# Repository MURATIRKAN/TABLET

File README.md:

# TABLET
LOKUM-MINI TABLET ALLWINNER A33 ARM-CPU

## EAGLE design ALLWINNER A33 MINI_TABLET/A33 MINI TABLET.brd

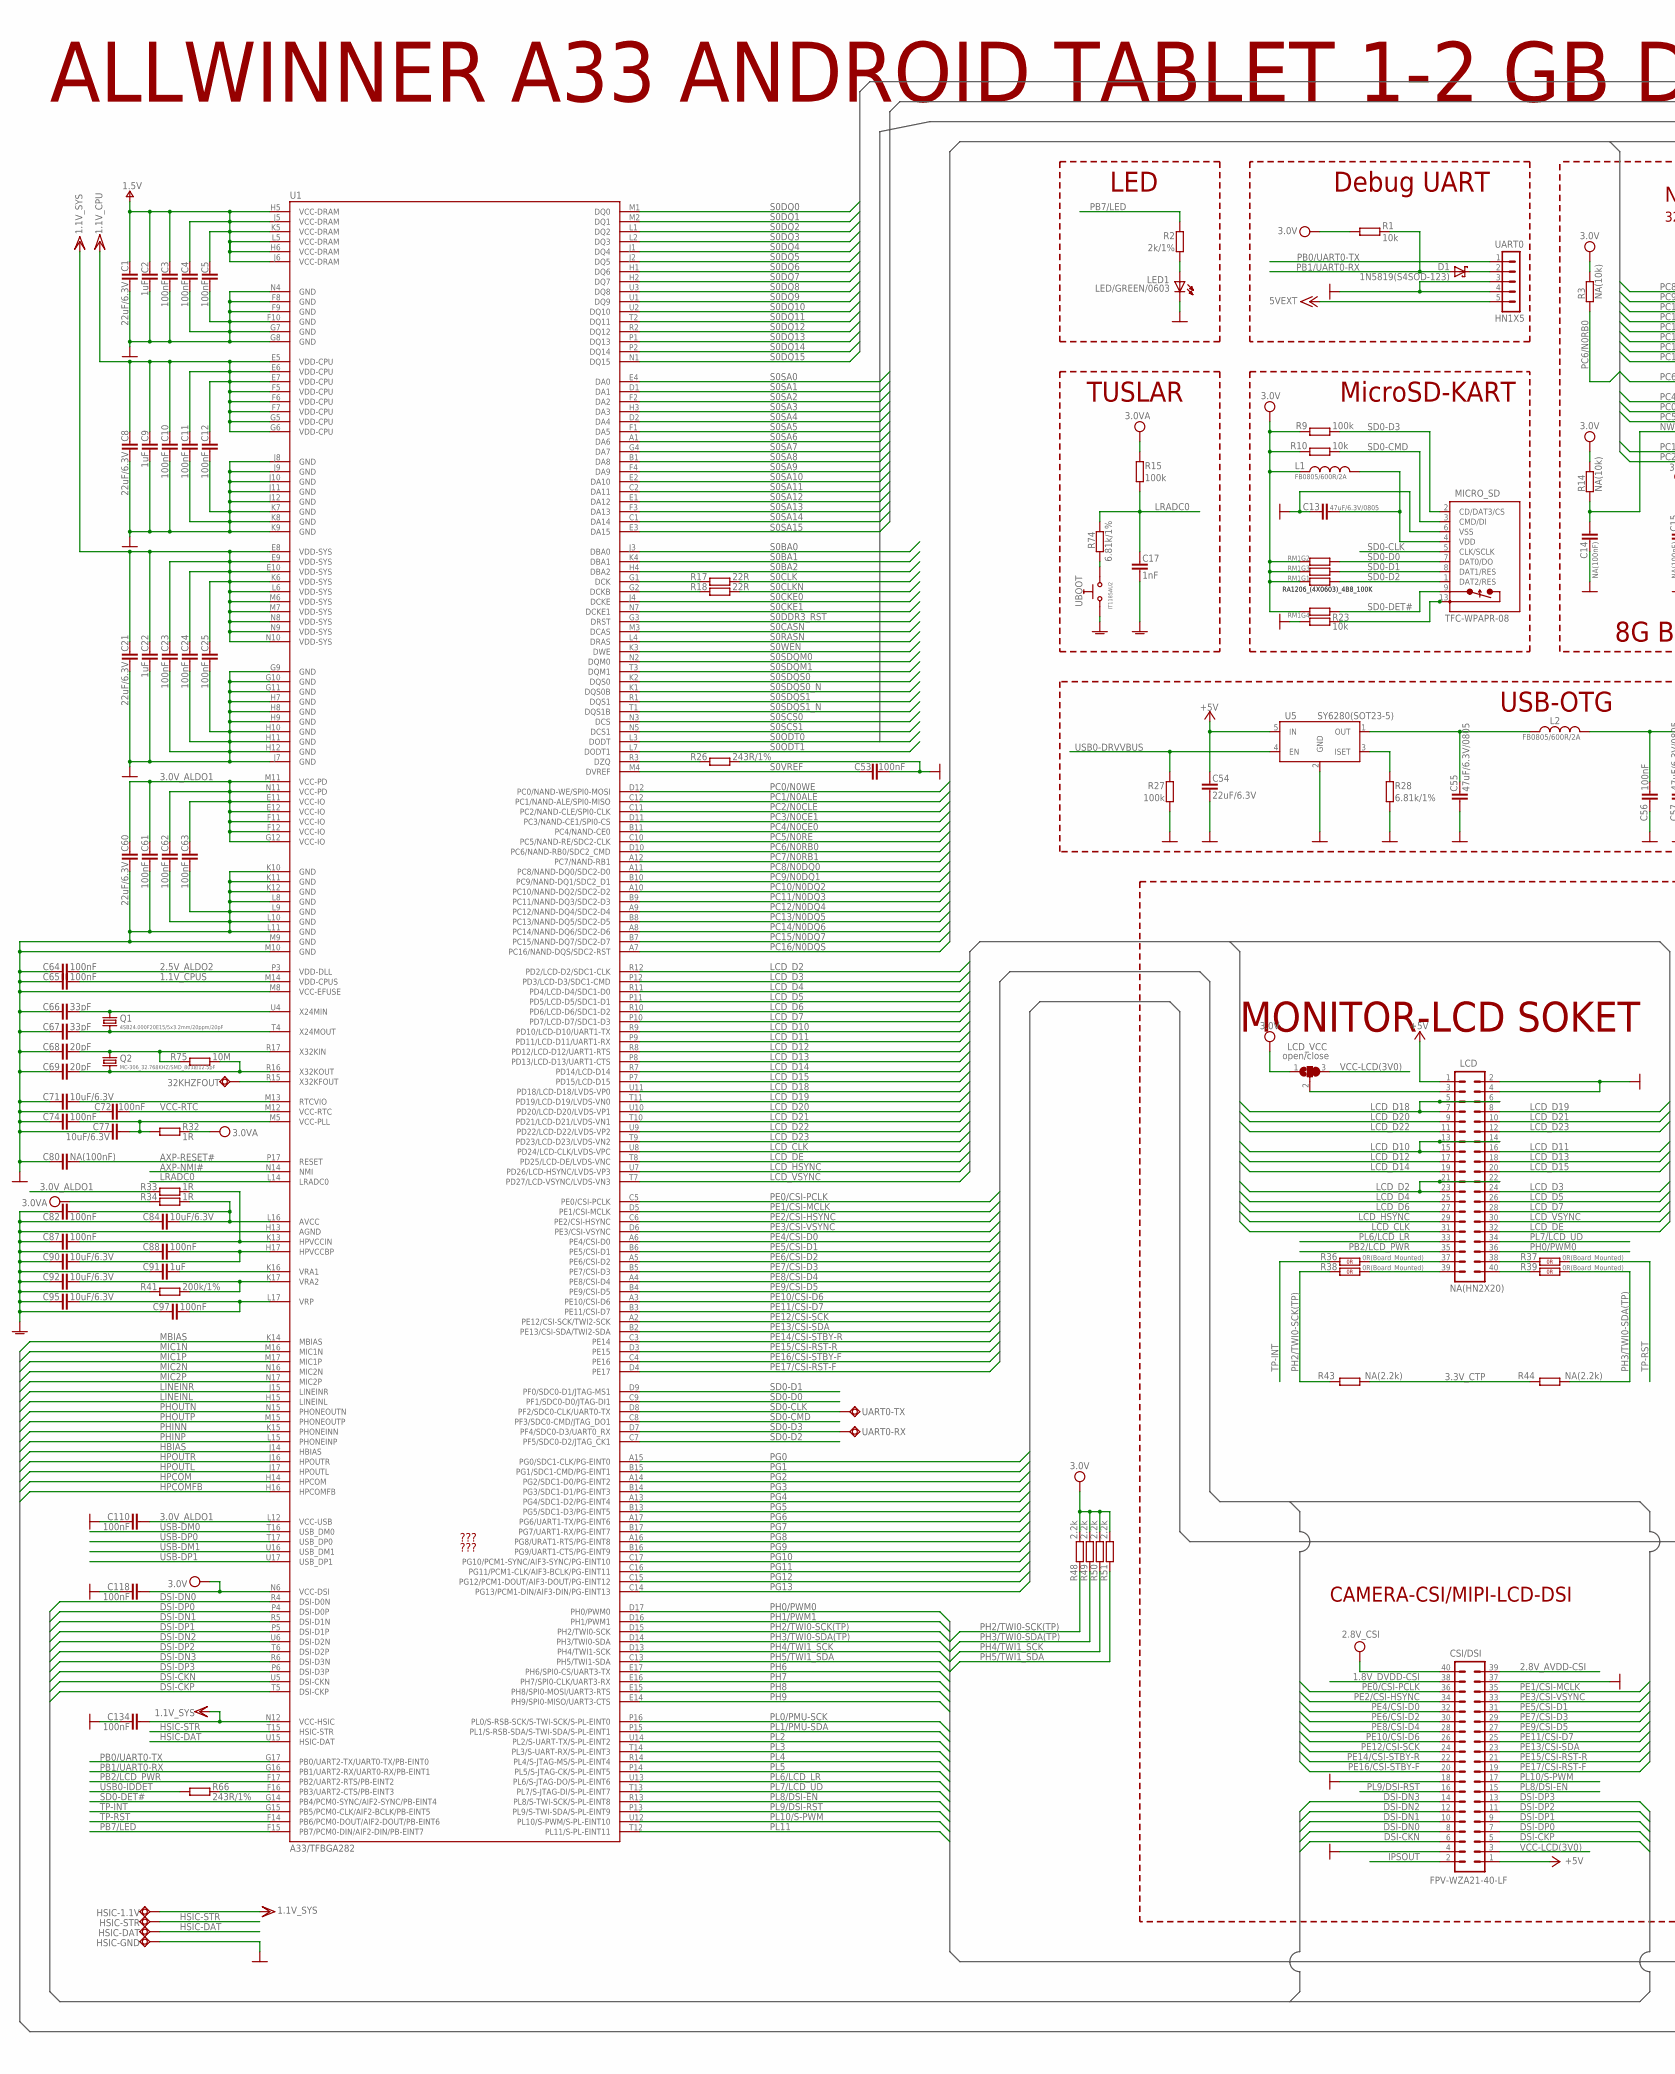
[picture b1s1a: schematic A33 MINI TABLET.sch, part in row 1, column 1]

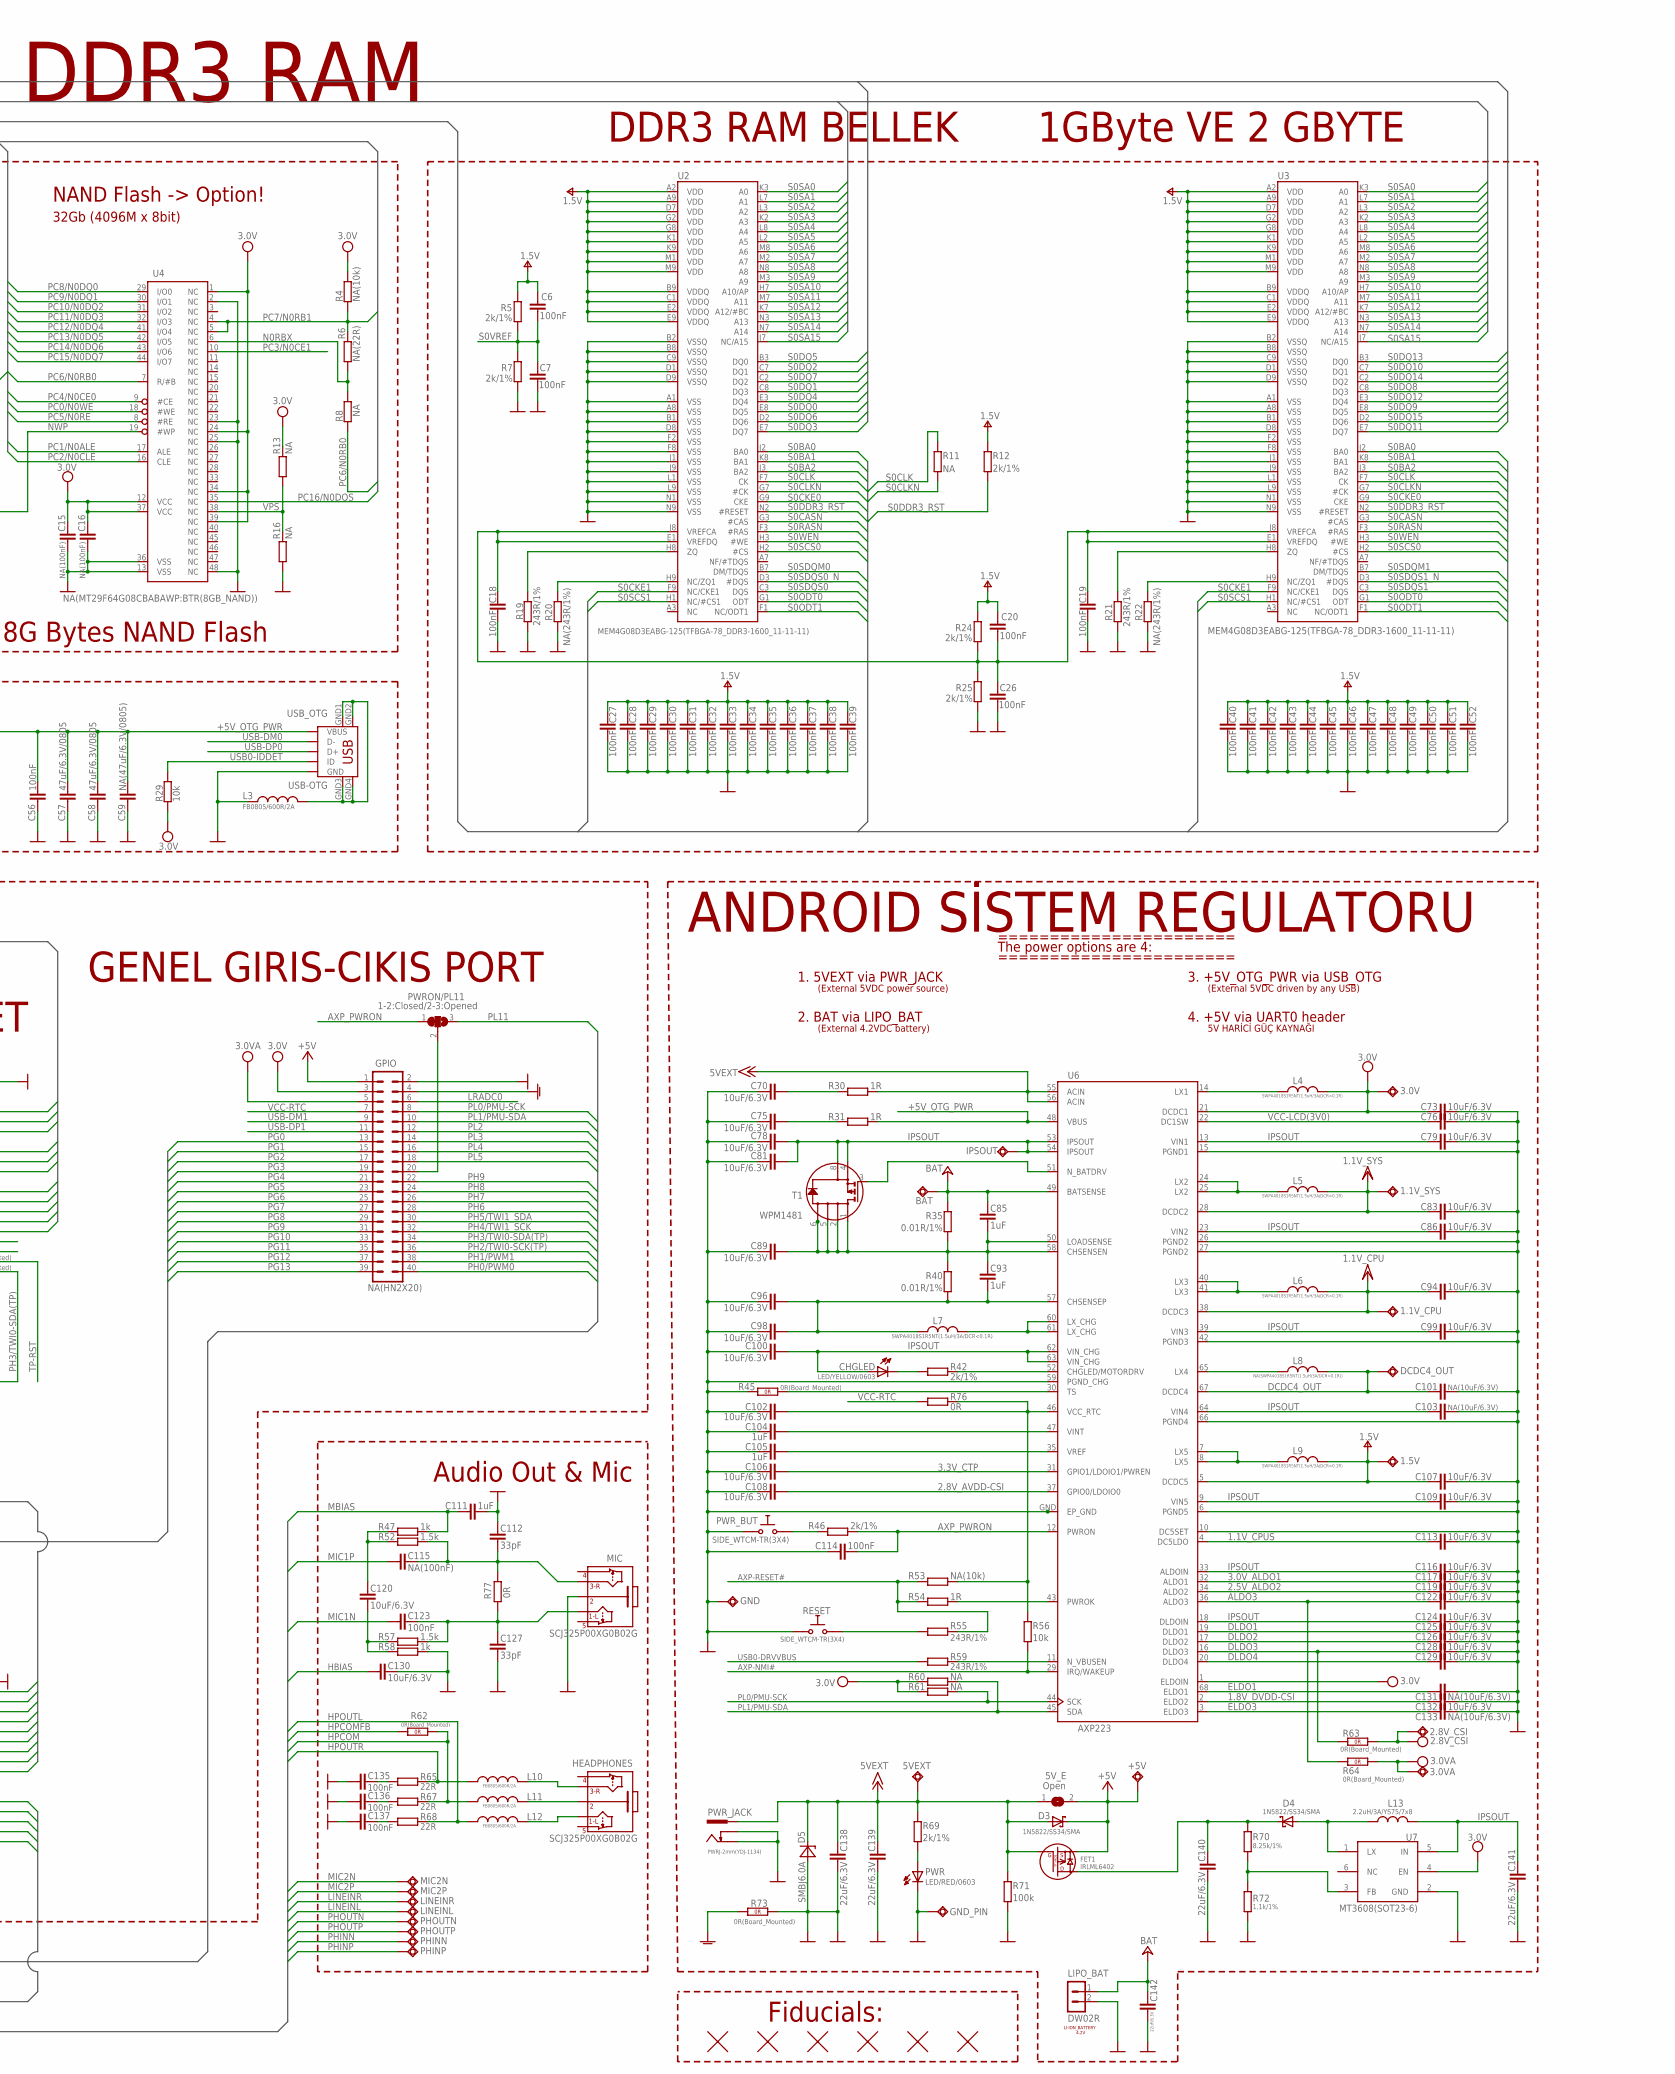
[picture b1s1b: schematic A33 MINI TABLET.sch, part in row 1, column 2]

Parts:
1.1V_CPU, 1.1V_SYS, 1.5V, 2.8V_CSI, 3.0V, 3.0VA, 5VEXT, 32KHZFOUT: TESTPADTESTPAD_40-ROUND; TESTPAD_40-ROUND
5V_E: Open; SJ_1_SMALLER
+5V: TESTPADTESTPAD_40-ROUND; TESTPAD_40-ROUND
BAT: TESTPADTESTPAD_40-ROUND; TESTPAD_40-ROUND
C1, C8, C21, C54, C60, C138, C139, C140, C141, C142: 22uF/6.3V; C0603_DWS
C2, C9, C22, C85, C91, C93, C104, C105, C111: 1uF; C0603_DWS
C3, C4, C5, C6, C7, C10, C11, C12, C18, C19, C20, C23, C24, C25, C26, C27, C28, C29, C30, C31, C32, C33, C34, C35, C36, C37, C38, C39, C40, C41, C42, C43, C44, C45, C46, C47, C48, C49, C50, C51, C52, C53, C56, C61, C62, C63, C64, C65, C72, C74, C82, C87, C88, C97, C110, C114, C118, C123, C134, C135, C136, C137: 100nF; C0402_TI
C13, C55, C57, C58: 47uF/6.3V/0805; C0805_5MIL_DWS
C14, C15, C16, C80, C115: NA(100nF); C0402_TI
C17: 1nF; C0603_DWS
C59: NA(47uF/6.3V/0805); C0805_5MIL_DWS
C66, C67, C112, C127: 33pF; C0603_DWS
C68, C69: 20pF; C0603_DWS
C70, C71, C73, C75, C76, C77, C78, C79, C81, C83, C84, C86, C89, C90, C92, C94, C95, C96, C98, C99, C100, C102, C106, C107, C108, C109, C113, C116, C117, C119, C120, C122, C124, C125, C126, C128, C129, C130, C132: 10uF/6.3V; C0603_DWS
C101, C103, C131, C133: NA(10uF/6.3V); C0603_DWS
CHGLED: LED/YELLOW/0603; LED-0603_TEST
CSI/DSI: FPV-WZA21-40-LF
D1: 1N5819(S4SOD-123); SOD-123
D3, D4: 1N5822/SS34/SMA; MLL-41
D5: SMBJ6.0A; DO214AA
DCDC4_OUT: TESTPADTESTPAD_40-ROUND; TESTPAD_40-ROUND
FET1: IRLML6402; SOT23
GND: TESTPADTESTPAD_40-ROUND; TESTPAD_40-ROUND
GND_PIN: TESTPAD3; TEST_PAD40/70/SQUARE
GPIO: NA(HN2X20); HN2X20-MALE
HEADPHONES: SCJ325P00XG0B02G
HSIC-1.1V: TESTPADTESTPAD_40-ROUND; TESTPAD_40-ROUND
HSIC-DAT: TESTPADTESTPAD_40-ROUND; TESTPAD_40-ROUND
HSIC-GND: TESTPADTESTPAD_40-ROUND; TESTPAD_40-ROUND
HSIC-STR: TESTPADTESTPAD_40-ROUND; TESTPAD_40-ROUND
IPSOUT: TESTPADTESTPAD_40-ROUND; TESTPAD_40-ROUND
L1, L2, L3, L10, L11, L12: FB0805/600R/2A; L0805_5MIL_DWS
L4, L5, L6, L7, L9: SWPA4018S1R5NT(1.5uH/3A/DCR<0.1R); SWPA4018S
L8: NA(SWPA4018S1R5NT(1.5uH/3A/DCR<0.1R)); SWPA4018S
L13: 2.2uH/3A/YS75/7x8; 8X8MM_3131
LCD: NA(HN2X20); HN2X20-MALE
LCD_VCC: open/close; SJ_2_SMALL_23_TIED
LED1: LED/GREEN/0603; LED-0603_TEST
LINEINL: TESTPADTESTPAD_40-ROUND; TESTPAD_40-ROUND
LINEINR: TESTPADTESTPAD_40-ROUND; TESTPAD_40-ROUND
LIPO_BAT: DW02R
MIC: SCJ325P00XG0B02G
MIC2N, MIC2P: TESTPADTESTPAD_40-ROUND; TESTPAD_40-ROUND
MICRO_SD: TFC-WPAPR-08
PHINN: TESTPADTESTPAD_40-ROUND; TESTPAD_40-ROUND
PHINP: TESTPADTESTPAD_40-ROUND; TESTPAD_40-ROUND
PHOUTN: TESTPADTESTPAD_40-ROUND; TESTPAD_40-ROUND
PHOUTP: TESTPADTESTPAD_40-ROUND; TESTPAD_40-ROUND
PWR: LED/RED/0603; LED-0603_TEST
PWRON/PL11: 1-2:Closed/2-3:Opened; SJ_2_SMALL_12_TIED
PWR_BUT: SIDE_WTCM-TR(3X4); SW_TAKT3X4
PWR_JACK: PWRJ-2mm(YDJ-1134); PWR_JACK_UNI_MILLING
Q1: 4SB24.000F20E15/5x3.2mm/20ppm/20pF; HCX-4S
Q2: MC-306_32.768KHZ/SMD_8038/12.5pF; MC-306
R1, R10, R23, R29, R56: 10k; R0603_5MIL_DWS
R2, R5, R7, R12, R24, R25, R42, R46, R69: 2k/1%; R0603_5MIL_DWS
R3, R4, R14, R53: NA(10k); R0603_5MIL_DWS
R6: NA(22R); R0402_TI
R8, R13, R16, R60, R61: NA; R0603_5MIL_DWS
R9, R15, R27, R71: 100k; R0603_5MIL_DWS
R11: NA; R0402_TI
R17, R18, R65, R67, R68: 22R; R0402_TI
R19, R21, R26, R55, R59, R66: 243R/1%; R0603_5MIL_DWS
R20, R22: NA(243R/1%); R0603_5MIL_DWS
R28, R74: 6.81k/1%; R0603_5MIL_DWS
R30, R31, R32, R33, R34, R54: 1R; R0603_5MIL_DWS
R35, R40: 0.01R/1%; R1206_5MIL_WS
R36, R37, R38, R39, R45, R62, R63, R64, R73: 0R(Board_Mounted); 0603_0R
R41: 200k/1%; R0603_5MIL_DWS
R43, R44: NA(2.2k); R0603_5MIL_DWS
R47, R58: 1k; R0603_5MIL_DWS
R48, R49, R50, R51: 2.2k; R0603_5MIL_DWS
R52, R57: 1.5k; R0603_5MIL_DWS
R70: 8.25k/1%; R0603_5MIL_DWS
R72: 1.1k/1%; R0603_5MIL_DWS
R75: 10M; R0402_SMALL
R76: 0R; R1206_5MIL
R77: 0R; R0603_5MIL_DWS
RESET: SIDE_WTCM-TR(3X4); SW_TAKT3X4
RM1: RA1206_(4X0603)_4B8_100K; R_MATRIX_4
T1: WPM1481; DFN2*2-6L
U1: A33/TFBGA282; TFBGA282
U2, U3: MEM4G08D3EABG-125(TFBGA-78_DDR3-1600_11-11-11); FBGA78
U4: NA(MT29F64G08CBABAWP:BTR(8GB_NAND)); TSOP48
U5: SY6280(SOT23-5); SOT23-5
U6: AXP223; QFN68-8X8-04
U7: MT3608(SOT23-6); SOT23-6
U8, U9, U10, U11, U12, U13: FIDUCIAL; FIDUCIAL-1X3
UART0: HN1X5
UART0-RX, UART0-TX: TESTPADTESTPAD_40-ROUND; TESTPAD_40-ROUND
UBOOT: IT1185AU2
USB_OTG: USB-OTG; USB_MINI_9PIN

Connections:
1.1V_CPUS: C65.2, C113.2, U1.M14 (VDD-CPUS), U6.4 (DC5LDO)
1.8V_DVDD-CSI: C132.2, CSI/DSI.38, U6.2 (ELDO2)
2.5V_ALDO2: C64.2, C119.2, U1.P3 (VDD-DLL), U6.34 (ALDO2)
2.8V_AVDD-CSI: C108.2, CSI/DSI.39, U6.37 (GPIO0/LDOIO0)
3.0V_ALDO1: C60.1, C61.2, C62.2, C63.2, C110.2, C117.2, R33.1, U1.E11 (VCC-IO), U1.E12 (VCC-IO), U1.F11 (VCC-IO), U1.F12 (VCC-IO), U1.G12 (VCC-IO), U1.L12 (VCC-USB), U1.M11 (VCC-PD), U1.N11 (VCC-PD), U6.32 (ALDO1)
3.3V_CTP: C106.2, R43.1, R44.2, U6.31 (GPIO1/LDOIO1/PWREN)
+5V: 5V_E.2, +5V.1, C54.1, CSI/DSI.1, D3.K (C), FET1.2 (S), GPIO.1, LCD.1, U5.5 (IN)
+5V_OTG_PWR: C56.1, C57.1, C58.1, C59.1, L2.1, R31.2, U6.48 (VBUS), USB_OTG.VBUS
+15V: 5VEXT.1, 5V_E.1, C138.1, C139.1, D3.A, D5.C, FET1.1 (G), PWR_JACK.+, R30.2, R69.1, R71.1, U6.55 (ACIN), U6.56 (ACIN), UART0.5
+24V: BAT.1, C85.2, C142.2, LIPO_BAT.1, R35.2, U6.49 (BATSENSE)
ALDO3: C122.2, R64.2 (1.2), U6.36 (ALDO3)
AXP-NMI#: R56.1, U1.N14 (NMI), U6.29 (IRQ/WAKEUP)
AXP-RESET#: C80.2, R53.1, R54.1, R55.2, U1.P17 (RESET)
AXP_PWRON: C114.2, PWRON/PL11.1, R46.2, U6.12 (PWRON)
CHGLED: R42.2, U6.52 (CHGLED/MOTORDRV)
DCDC4_OUT: C101.2, DCDC4_OUT.1, L8.1, U6.67 (DCDC4)
DLDO1: C125.2, U6.19 (DLDO1)
DLDO2: C126.2, U6.17 (DLDO2)
DLDO3: C128.2, R63.2 (1.2), U6.16 (DLDO3)
DLDO4: C129.2, U6.20 (DLDO4)
DSI-CKN: CSI/DSI.6, U1.U5 (DSI-CKN)
DSI-CKP: CSI/DSI.5, U1.T5 (DSI-CKP)
DSI-DN0: CSI/DSI.8, U1.R4 (DSI-D0N)
DSI-DN1: CSI/DSI.10, U1.R5 (DSI-D1N)
DSI-DN2: CSI/DSI.12, U1.U6 (DSI-D2N)
DSI-DN3: CSI/DSI.14, U1.R6 (DSI-D3N)
DSI-DP0: CSI/DSI.7, U1.P4 (DSI-D0P)
DSI-DP1: CSI/DSI.9, U1.P5 (DSI-D1P)
DSI-DP2: CSI/DSI.11, U1.T6 (DSI-D2P)
DSI-DP3: CSI/DSI.13, U1.P6 (DSI-D3P)
ELDO1: C131.2, U6.68 (ELDO1)
ELDO3: C133.2, U6.3 (ELDO3)
GND: C1.2, C2.1, C3.1, C4.1, C5.1, C7.1, C8.2, C9.2, C10.1, C11.1, C12.1, C13.1, C14.1, C15.1, C16.1, C18.1, C19.1, C21.2, C22.2, C23.1, C24.1, C25.1, C26.1, C27.1, C28.1, C29.1, C30.1, C31.1, C32.1, C33.1, C34.1, C35.1, C36.1, C37.1, C38.1, C39.1, C40.1, C41.1, C42.1, C43.1, C44.1, C45.1, C46.1, C47.1, C48.1, C49.1, C50.1, C51.1, C52.1, C53.1, C54.2, C55.2, C56.2, C57.2, C58.2, C59.2, C60.2, C61.1, C62.1, C63.1, C64.1, C65.1, C66.1, C67.1, C68.1, C69.1, C70.1, C71.2, C72.2, C73.1, C74.2, C75.1, C76.1, C77.1, C78.1, C79.1, C80.1, C81.1, C83.1, C86.1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
GNDA: C17.2, C82.1, C84.2, C87.1, C88.1, C90.1, C91.1, C92.1, C95.1, C97.1, GPIO.4, R41.2, R73.2 (1.2), U1.H13 (AGND), UBOOT.1 (0)
HBIAS: C130.2, U1.J14 (HBIAS)
HPCOM: L11.1, R62.1 (1.1), R67.2, U1.H14 (HPCOM)
HPCOMFB: R62.2 (1.2), U1.H16 (HPCOMFB)
HPOUTL: L12.1, R68.2, U1.J17 (HPOUTL)
HPOUTR: L10.1, R65.2, U1.J16 (HPOUTR)
HPVCCIN: C87.2, R33.2, U1.K13 (HPVCCIN)
HSIC-DAT: HSIC-DAT.1, U1.U15 (HSIC-DAT)
HSIC-STR: HSIC-STR.1, U1.T15 (HSIC-STR)
IPSOUT: C78.2, C79.2, C81.2, C86.2, C99.2, C100.2, C103.2, C109.2, C116.2, C124.2, C141.2, CHGLED.A, CSI/DSI.2, IPSOUT.1, L13.1, T1.4 (S), T1.8 (S1), U6.9 (VIN5), U6.13 (VIN1), U6.18 (DLDOIN), U6.23 (VIN2), U6.33 (ALDOIN), U6.39 (VIN3), U6.53 (IPSOUT), U6.54 (IPSOUT), U6.62 (VIN_CHG), U6.63 (VIN_CHG), U6.64 (VIN4), U7.5 (IN)
LCD_CLK: LCD.31, U1.U8 (PD24/LCD-CLK/LVDS-VPC)
LCD_D2: LCD.21, LCD.22, LCD.23, U1.R12 (PD2/LCD-D2/SDC1-CLK)
LCD_D3: LCD.24, U1.P12 (PD3/LCD-D3/SDC1-CMD)
LCD_D4: LCD.25, U1.R11 (PD4/LCD-D4/SDC1-D0)
LCD_D5: LCD.26, U1.P11 (PD5/LCD-D5/SDC1-D1)
LCD_D6: LCD.27, U1.R10 (PD6/LCD-D6/SDC1-D2)
LCD_D7: LCD.28, U1.P10 (PD7/LCD-D7/SDC1-D3)
LCD_D10: LCD.13, LCD.14, LCD.15, U1.R9 (PD10/LCD-D10/UART1-TX)
LCD_D11: LCD.16, U1.P9 (PD11/LCD-D11/UART1-RX)
LCD_D12: LCD.17, U1.R8 (PD12/LCD-D12/UART1-RTS)
LCD_D13: LCD.18, U1.P8 (PD13/LCD-D13/UART1-CTS)
LCD_D14: LCD.19, U1.R7 (PD14/LCD-D14)
LCD_D15: LCD.20, U1.P7 (PD15/LCD-D15)
LCD_D18: LCD.5, LCD.6, LCD.7, U1.U11 (PD18/LCD-D18/LVDS-VP0)
LCD_D19: LCD.8, U1.T11 (PD19/LCD-D19/LVDS-VN0)
LCD_D20: LCD.9, U1.U10 (PD20/LCD-D20/LVDS-VP1)
LCD_D21: LCD.10, U1.T10 (PD21/LCD-D21/LVDS-VN1)
LCD_D22: LCD.11, U1.U9 (PD22/LCD-D22/LVDS-VP2)
LCD_D23: LCD.12, U1.T9 (PD23/LCD-D23/LVDS-VN2)
LCD_DE: LCD.32, U1.T8 (PD25/LCD-DE/LVDS-VNC)
LCD_HSYNC: LCD.29, U1.U7 (PD26/LCD-HSYNC/LVDS-VP3)
LCD_VSYNC: LCD.30, U1.T7 (PD27/LCD-VSYNC/LVDS-VN3)
LINEINL: LINEINL.1, U1.H15 (LINEINL)
LINEINR: LINEINR.1, U1.J15 (LINEINR)
LRADC0: C17.1, GPIO.6, R15.2, R74.1, U1.L14 (LRADC0)
MBIAS: C111.1, R47.2, U1.K14 (MBIAS)
MIC1N: C123.2, U1.M16 (MIC1N)
MIC1P: C115.2, U1.M17 (MIC1P)
MIC2N: MIC2N.1, U1.N16 (MIC2N)
MIC2P: MIC2P.1, U1.N17 (MIC2P)
N0RBX: R6.2, R8.1, U4.6 (NC)
unnamed: R59.2, U6.11 (N_VBUSEN)
unnamed: R26.2, U1.R3 (DZQ)
unnamed: R19.2, U2.H8 (ZQ)
unnamed: L4.2, U6.14 (LX1)
unnamed: R21.2, U3.H8 (ZQ)
unnamed: L3.2, USB_OTG.GND1, USB_OTG.GND2, USB_OTG.GND3, USB_OTG.GND4
unnamed: D1.C, UART0.2
unnamed: R17.2, U1.G1 (DCK)
unnamed: R18.2, U1.G2 (DCKB)
unnamed: R66.2, U1.F16 (PB3/UART2-CTS/PB-EINT3)
unnamed: R28.2, U5.3 (ISET)
unnamed: C55.1, L2.2, U5.1 (OUT)
unnamed: R22.2, U3.H9 (NC/ZQ1)
unnamed: R45.1 (1.1), U6.30 (TS)
unnamed: T1.3 (G), U6.51 (N_BATDRV)
unnamed: C104.2, U6.47 (VINT)
unnamed: C85.1, C89.2, C93.2, R35.1, R40.2, T1.1 (D), T1.2 (D1), T1.5 (D2), T1.6 (D3), T1.7 (D4), U6.50 (LOADSENSE), U6.58 (CHSENSEN)
unnamed: L7.1, U6.60 (LX_CHG), U6.61 (LX_CHG)
unnamed: C88.2, C90.2, U1.H17 (HPVCCBP)
unnamed: LCD.3, LCD_VCC.2
unnamed: C93.1, C96.2, C98.2, L7.2, R40.1, U6.57 (CHSENSEP)
unnamed: C105.2, U6.35 (VREF)
unnamed: C140.1, D4.K (C), FET1.3 (D), R70.2
unnamed: R55.1, RESET.2_1 (0)
unnamed: LCD.37, R36.1 (1.1)
unnamed: LCD.39, R38.1 (1.1)
unnamed: LCD.38, R37.2 (1.2)
unnamed: C91.2, U1.K16 (VRA1)
unnamed: LCD.40, R39.2 (1.2)
unnamed: L5.2, U6.24 (LX2), U6.25 (LX2)
unnamed: C82.2, C84.1, R34.2, U1.L16 (AVCC)
unnamed: L6.2, U6.40 (LX3), U6.41 (LX3)
unnamed: C123.1, C127.2, MIC.1, R57.2, R77.1
unnamed: C137.2, R68.1
unnamed: L8.2, U6.65 (LX4)
unnamed: C136.2, R67.1
unnamed: L9.2, U6.7 (LX5), U6.8 (LX5)
unnamed: PWR_BUT.1_1 (1), R46.1
unnamed: R74.2, UBOOT.2 (1)
unnamed: HEADPHONES.2, L11.2
unnamed: HEADPHONES.1, L12.2
unnamed: C71.1, U1.M13 (RTCVIO)
unnamed: CHGLED.C, R42.1
unnamed: C135.2, R65.1
unnamed: HEADPHONES.3, L10.2
unnamed: C112.2, C115.1, MIC.3, R52.2, R77.2
unnamed: C120.2, R47.1, R52.1
unnamed: C120.1, R57.1, R58.1
unnamed: R20.2, U2.H9 (NC/ZQ1)
unnamed: C18.2, C19.2, C20.2, C26.2, R24.1, R25.2, U2.E1 (VREFDQ), U2.J8 (VREFCA), U3.E1 (VREFDQ), U3.J8 (VREFCA)
unnamed: GPIO.20, PWRON/PL11.2
unnamed: 32KHZFOUT.1, U1.R15 (X32KFOUT)
unnamed: MICRO_SD.10 (PACK1), MICRO_SD.11 (PACK2), MICRO_SD.12 (PACK3), MICRO_SD.13 (PACK4), R23.1
unnamed: C68.2, Q2.4 (2), R75.1, U1.R17 (X32KIN)
unnamed: C69.2, Q2.1, R75.2, U1.R16 (X32KOUT)
unnamed: C95.2, C97.2, U1.L17 (VRP)
unnamed: D4.A, L13.2, U7.1 (LX)
unnamed: R70.1, R72.1, U7.3 (FB)
unnamed: PWR.A, R69.2
unnamed: C70.2, R30.1
unnamed: C75.2, R31.1
unnamed: C92.2, R41.1, U1.K17 (VRA2)
unnamed: LED1.A, R2.2
NWP: C14.2, R14.2, U4.19 (#WP)
PB0/UART0-TX: U1.G17 (PB0/UART2-TX/UART0-TX/PB-EINT0), UART0.1
PB1/UART0-RX: D1.A, R1.1, U1.G16 (PB1/UART2-RX/UART0-RX/PB-EINT1)
PB2/LCD_PWR: LCD.35, U1.F17 (PB2/UART2-RTS/PB-EINT2)
PB7/LED: R2.1, U1.F15 (PB7/PCM0-DIN/AIF2-DIN/PB-EINT7)
PC0/N0WE: U1.D12 (PC0/NAND-WE/SPI0-MOSI), U4.18 (#WE)
PC1/N0ALE: U1.C12 (PC1/NAND-ALE/SPI0-MISO), U4.17 (ALE)
PC2/N0CLE: U1.C11 (PC2/NAND-CLE/SPI0-CLK), U4.16 (CLE)
PC3/N0CE1: U1.D11 (PC3/NAND-CE1/SPI0-CS), U4.10 (NC)
PC4/N0CE0: U1.B11 (PC4/NAND-CE0), U4.9 (#CE)
PC5/N0RE: U1.C10 (PC5/NAND-RE/SDC2-CLK), U4.8 (#RE)
PC6/N0RB0: R3.2, R8.2, U1.D10 (PC6/NAND-RB0/SDC2_CMD), U4.7 (R/#B)
PC7/N0RB1: R4.2, R6.1, U1.A12 (PC7/NAND-RB1), U4.4 (NC), U4.5 (NC)
PC8/N0DQ0: U1.A11 (PC8/NAND-DQ0/SDC2-D0), U4.29 (I/O0)
PC9/N0DQ1: U1.B10 (PC9/NAND-DQ1/SDC2_D1), U4.30 (I/O1)
PC10/N0DQ2: U1.A10 (PC10/NAND-DQ2/SDC2-D2), U4.31 (I/O2)
PC11/N0DQ3: U1.B9 (PC11/NAND-DQ3/SDC2-D3), U4.32 (I/O3)
PC12/N0DQ4: U1.A9 (PC12/NAND-DQ4/SDC2-D4), U4.41 (I/O4)
PC13/N0DQ5: U1.B8 (PC13/NAND-DQ5/SDC2-D5), U4.42 (I/O5)
PC14/N0DQ6: U1.A8 (PC14/NAND-DQ6/SDC2-D6), U4.43 (I/O6)
PC15/N0DQ7: U1.B7 (PC15/NAND-DQ7/SDC2-D7), U4.44 (I/O7)
PC16/N0DQS: U1.A7 (PC16/NAND-DQS/SDC2-RST), U4.35 (NC)
PE0/CSI-PCLK: CSI/DSI.36, U1.C5 (PE0/CSI-PCLK)
PE1/CSI-MCLK: CSI/DSI.35, U1.D5 (PE1/CSI-MCLK)
PE2/CSI-HSYNC: CSI/DSI.34, U1.C6 (PE2/CSI-HSYNC)
PE3/CSI-VSYNC: CSI/DSI.33, U1.D6 (PE3/CSI-VSYNC)
PE4/CSI-D0: CSI/DSI.32, U1.A6 (PE4/CSI-D0)
PE5/CSI-D1: CSI/DSI.31, U1.B6 (PE5/CSI-D1)
PE6/CSI-D2: CSI/DSI.30, U1.A5 (PE6/CSI-D2)
PE7/CSI-D3: CSI/DSI.29, U1.B5 (PE7/CSI-D3)
PE8/CSI-D4: CSI/DSI.28, U1.A4 (PE8/CSI-D4)
PE9/CSI-D5: CSI/DSI.27, U1.B4 (PE9/CSI-D5)
PE10/CSI-D6: CSI/DSI.26, U1.A3 (PE10/CSI-D6)
PE11/CSI-D7: CSI/DSI.25, U1.B3 (PE11/CSI-D7)
PE12/CSI-SCK: CSI/DSI.24, U1.A2 (PE12/CSI-SCK/TWI2-SCK)
PE13/CSI-SDA: CSI/DSI.23, U1.B2 (PE13/CSI-SDA/TWI2-SDA)
PE14/CSI-STBY-R: CSI/DSI.22, U1.C3 (PE14)
PE15/CSI-RST-R: CSI/DSI.21, U1.D3 (PE15)
PE16/CSI-STBY-F: CSI/DSI.20, U1.C4 (PE16)
PE17/CSI-RST-F: CSI/DSI.19, U1.D4 (PE17)
PG0: GPIO.13, U1.A15 (PG0/SDC1-CLK/PG-EINT0)
PG1: GPIO.15, U1.B15 (PG1/SDC1-CMD/PG-EINT1)
PG2: GPIO.17, U1.A14 (PG2/SDC1-D0/PG-EINT2)
PG3: GPIO.19, U1.B14 (PG3/SDC1-D1/PG-EINT3)
PG4: GPIO.21, U1.A13 (PG4/SDC1-D2/PG-EINT4)
PG5: GPIO.23, U1.B13 (PG5/SDC1-D3/PG-EINT5)
PG6: GPIO.25, U1.A17 (PG6/UART1-TX/PG-EINT6)
PG7: GPIO.27, U1.B17 (PG7/UART1-RX/PG-EINT7)
PG8: GPIO.29, U1.A16 (PG8/URAT1-RTS/PG-EINT8)
PG9: GPIO.31, U1.B16 (PG9/UART1-CTS/PG-EINT9)
PG10: GPIO.33, U1.C17 (PG10/PCM1-SYNC/AIF3-SYNC/PG-EINT10)
PG11: GPIO.35, U1.C16 (PG11/PCM1-CLK/AIF3-BCLK/PG-EINT11)
PG12: GPIO.37, U1.C15 (PG12/PCM1-DOUT/AIF3-DOUT/PG-EINT12)
PG13: GPIO.39, U1.C14 (PG13/PCM1-DIN/AIF3-DIN/PG-EINT13)
PH0/PWM0: GPIO.40, LCD.36, U1.D17 (PH0/PWM0)
PH1/PWM1: GPIO.38, U1.D16 (PH1/PWM1)
PH2/TWI0-SCK(TP): GPIO.36, R38.2 (1.2), R43.2, R48.1, U1.D15 (PH2/TWI0-SCK)
PH3/TWI0-SDA(TP): GPIO.34, R39.1 (1.1), R44.1, R49.1, U1.D14 (PH3/TWI0-SDA)
PH4/TWI1_SCK: GPIO.32, R50.1, U1.D13 (PH4/TWI1-SCK)
PH5/TWI1_SDA: GPIO.30, R51.1, U1.C13 (PH5/TWI1-SDA)
PH6: GPIO.28, U1.E17 (PH6/SPI0-CS/UART3-TX)
PH7: GPIO.26, U1.E16 (PH7/SPI0-CLK/UART3-RX)
PH8: GPIO.24, U1.E15 (PH8/SPI0-MOSI/UART3-RTS)
PH9: GPIO.22, U1.E14 (PH9/SPI0-MISO/UART3-CTS)
PHINN: PHINN.1, U1.K15 (PHONEINN)
PHINP: PHINP.1, U1.L15 (PHONEINP)
PHOUTN: PHOUTN.1, U1.N15 (PHONEOUTN)
PHOUTP: PHOUTP.1, U1.M15 (PHONEOUTP)
PL0/PMU-SCK: GPIO.8, R61.2, U1.P16 (PL0/S-RSB-SCK/S-TWI-SCK/S-PL-EINT0), U6.44 (SCK)
PL1/PMU-SDA: GPIO.10, R60.2, U1.P15 (PL1/S-RSB-SDA/S-TWI-SDA/S-PL-EINT1), U6.45 (SDA)
PL2: GPIO.12, U1.U14 (PL2/S-UART-TX/S-PL-EINT2)
PL3: GPIO.14, U1.T14 (PL3/S-UART-RX/S-PL-EINT3)
PL4: GPIO.16, U1.R14 (PL4/S-JTAG-MS/S-PL-EINT4)
PL5: GPIO.18, U1.P14 (PL5/S-JTAG-CK/S-PL-EINT5)
PL6/LCD_LR: LCD.33, U1.U13 (PL6/S-JTAG-DO/S-PL-EINT6)
PL7/LCD_UD: LCD.34, U1.T13 (PL7/S-JTAG-DI/S-PL-EINT7)
PL8/DSI-EN: CSI/DSI.15, U1.R13 (PL8/S-TWI-SCK/S-PL-EINT8)
PL9/DSI-RST: CSI/DSI.16, U1.P13 (PL9/S-TWI-SDA/S-PL-EINT9)
PL10/S-PWM: CSI/DSI.17, U1.U12 (PL10/S-PWM/S-PL-EINT10)
PL11: PWRON/PL11.3, U1.T12 (PL11/S-PL-EINT11)
PWROK: R54.2, U6.43 (PWROK)
S0BA0: U1.J3 (DBA0), U2.J2 (BA0), U3.J2 (BA0)
S0BA1: U1.K4 (DBA1), U2.K8 (BA1), U3.K8 (BA1)
S0BA2: U1.H4 (DBA2), U2.J3 (BA2), U3.J3 (BA2)
S0CASN: U1.M3 (DCAS), U2.G3 (#CAS), U3.G3 (#CAS)
S0CKE0: U1.J4 (DCKE), U2.G9 (CKE), U3.G9 (CKE)
S0CKE1: U1.N7 (DCKE1), U2.F9 (NC/CKE1), U3.F9 (NC/CKE1)
S0CLK: R11.1, R17.1, U2.F7 (CK), U3.F7 (CK)
S0CLKN: R11.2, R18.1, U2.G7 (#CK), U3.G7 (#CK)
S0DDR3_RST: R12.2, U1.G3 (DRST), U2.N2 (#RESET), U3.N2 (#RESET)
S0DQ0: U1.M1 (DQ0), U2.E8 (DQ5)
S0DQ1: U1.M2 (DQ1), U2.C8 (DQ3)
S0DQ2: U1.L1 (DQ2), U2.C7 (DQ1)
S0DQ3: U1.L2 (DQ3), U2.E7 (DQ7)
S0DQ4: U1.J1 (DQ4), U2.E3 (DQ4)
S0DQ5: U1.J2 (DQ5), U2.B3 (DQ0)
S0DQ6: U1.H1 (DQ6), U2.D2 (DQ6)
S0DQ7: U1.H2 (DQ7), U2.C2 (DQ2)
S0DQ8: U1.U3 (DQ8), U3.C8 (DQ3)
S0DQ9: U1.U1 (DQ9), U3.E8 (DQ5)
S0DQ10: U1.U2 (DQ10), U3.C7 (DQ1)
S0DQ11: U1.T2 (DQ11), U3.E7 (DQ7)
S0DQ12: U1.R2 (DQ12), U3.E3 (DQ4)
S0DQ13: U1.P1 (DQ13), U3.B3 (DQ0)
S0DQ14: U1.P2 (DQ14), U3.C2 (DQ2)
S0DQ15: U1.N1 (DQ15), U3.D2 (DQ6)
S0ODT0: U1.L3 (DODT), U2.G1 (ODT), U3.G1 (ODT)
S0ODT1: U1.L7 (DODT1), U2.F1 (NC/ODT1), U3.F1 (NC/ODT1)
S0RASN: U1.L4 (DRAS), U2.F3 (#RAS), U3.F3 (#RAS)
S0SA0: U1.E4 (DA0), U2.K3 (A0), U3.K3 (A0)
S0SA1: U1.D1 (DA1), U2.L7 (A1), U3.L7 (A1)
S0SA2: U1.F2 (DA2), U2.L3 (A2), U3.L3 (A2)
S0SA3: U1.H3 (DA3), U2.K2 (A3), U3.K2 (A3)
S0SA4: U1.D2 (DA4), U2.L8 (A4), U3.L8 (A4)
S0SA5: U1.F1 (DA5), U2.L2 (A5), U3.L2 (A5)
S0SA6: U1.A1 (DA6), U2.M8 (A6), U3.M8 (A6)
S0SA7: U1.G4 (DA7), U2.M2 (A7), U3.M2 (A7)
S0SA8: U1.B1 (DA8), U2.N8 (A8), U3.N8 (A8)
S0SA9: U1.F4 (DA9), U2.M3 (A9), U3.M3 (A9)
S0SA10: U1.E2 (DA10), U2.H7 (A10/AP), U3.H7 (A10/AP)
S0SA11: U1.C2 (DA11), U2.M7 (A11), U3.M7 (A11)
S0SA12: U1.E1 (DA12), U2.K7 (A12/#BC), U3.K7 (A12/#BC)
S0SA13: U1.F3 (DA13), U2.N3 (A13), U3.N3 (A13)
S0SA14: U1.C1 (DA14), U2.N7 (A14), U3.N7 (A14)
S0SA15: U1.E3 (DA15), U2.J7 (NC/A15), U3.J7 (NC/A15)
S0SCS0: U1.N3 (DCS), U2.H2 (#CS), U3.H2 (#CS)
S0SCS1: U1.N5 (DCS1), U2.H1 (NC/#CS1), U3.H1 (NC/#CS1)
S0SDQM0: U1.N2 (DQM0), U2.B7 (DM/TDQS)
S0SDQM1: U1.T3 (DQM1), U3.B7 (DM/TDQS)
S0SDQS0: U1.K2 (DQS0), U2.C3 (DQS)
S0SDQS0_N: U1.K1 (DQS0B), U2.D3 (#DQS)
S0SDQS1: U1.R1 (DQS1), U3.C3 (DQS)
S0SDQS1_N: U1.T1 (DQS1B), U3.D3 (#DQS)
S0VREF: C6.2, C7.2, C53.2, R5.1, R7.2, U1.M4 (DVREF)
S0WEN: U1.K3 (DWE), U2.H3 (#WE), U3.H3 (#WE)
SD0-CLK: MICRO_SD.5 (CLK/SCLK), U1.D8 (PF2/SDC0-CLK/UART0-TX), UART0-TX.1
SD0-CMD: MICRO_SD.3 (CMD/DI), R10.1, U1.C8 (PF3/SDC0-CMD/JTAG_DO1)
SD0-D0: MICRO_SD.7 (DAT0/DO), RM1.2.1 (1), U1.C9 (PF1/SDC0-D0/JTAG-DI1)
SD0-D1: MICRO_SD.8 (DAT1/RES), RM1.3.1 (1), U1.D9 (PF0/SDC0-D1/JTAG-MS1)
SD0-D2: MICRO_SD.1 (DAT2/RES), RM1.1.1 (1), U1.C7 (PF5/SDC0-D2/JTAG_CK1)
SD0-D3: MICRO_SD.2 (CD/DAT3/CS), R9.1, U1.D7 (PF4/SDC0-D3/UART0_RX), UART0-RX.1
SD0-DET#: MICRO_SD.9 (CP_E), RM1.4.1 (1), U1.G14 (PB4/PCM0-SYNC/AIF2-SYNC/PB-EINT4)
SD_VCC: C13.2, L1.2, MICRO_SD.4 (VDD)
TP-INT: R36.2 (1.2), U1.G15 (PB5/PCM0-CLK/AIF2-BCLK/PB-EINT5)
TP-RST: R37.1 (1.1), U1.F14 (PB6/PCM0-DOUT/AIF2-DOUT/PB-EINT6)
USB0-DRVVBUS: R27.2, R59.1, U5.4 (EN)
USB0-IDDET: R29.2, R66.1, USB_OTG.ID
USB-DM0: U1.T16 (USB_DM0), USB_OTG.D-
USB-DM1: GPIO.9, U1.U16 (USB_DM1)
USB-DP0: U1.T17 (USB_DP0), USB_OTG.D+
USB-DP1: GPIO.11, U1.U17 (USB_DP1)
V+: 1.5V.1, C1.1, C2.2, C3.2, C4.2, C5.2, C6.1, C20.1, C27.2, C28.2, C29.2, C30.2, C31.2, C32.2, C33.2, C34.2, C35.2, C36.2, C37.2, C38.2, C39.2, C40.2, C41.2, C42.2, C43.2, C44.2, C45.2, C46.2, C47.2, C48.2, C49.2, C50.2, C51.2, C52.2, C107.2, L9.1, R5.2, R12.1, R24.2, U1.H5 (VCC-DRAM), U1.H6 (VCC-DRAM), U1.J5 (VCC-DRAM), U1.J6 (VCC-DRAM), U1.K5 (VCC-DRAM), U1.L5 (VCC-DRAM), U2.A2 (VDD), U2.A9 (VDD), U2.B9 (VDDQ), U2.C1 (VDDQ), U2.D7 (VDD), U2.E2 (VDDQ), U2.E9 (VDDQ), U2.G2 (VDD), U2.G8 (VDD), U2.K1 (VDD), U2.K9 (VDD), U2.M1 (VDD), U2.M9 (VDD), U3.A2 (VDD), U3.A9 (VDD), U3.B9 (VDDQ), U3.C1 (VDDQ), U3.D7 (VDD), U3.E2 (VDDQ), U3.E9 (VDDQ), U3.G2 (VDD), U3.G8 (VDD), U3.K1 (VDD), U3.K9 (VDD), U3.M1 (VDD), U3.M9 (VDD), U6.5 (DCDC5)
VCC: 3.0V.1, C15.2, C16.2, C73.2, C118.2, GPIO.3, L1.1, L4.1, LCD_VCC.1, R1.2, R3.1, R4.1, R9.2, R10.2, R13.1, R14.1, R29.1, R48.2, R49.2, R50.2, R51.2, R60.1, R61.1, RM1.1.2 (2), RM1.2.2 (2), RM1.3.2 (2), RM1.4.2 (2), U1.N6 (VCC-DSI), U4.1 (NC), U4.12 (VCC), U4.24 (NC), U4.34 (NC), U4.37 (VCC), U4.39 (NC), U6.1 (ELDOIN), U6.21 (DCDC1), U7.4 (EN)
VCC-LCD(3V0): C76.2, CSI/DSI.3, LCD_VCC.3, U6.22 (DC1SW)
VCC-PLL: C74.1, C77.2, R32.1, U1.M5 (VCC-PLL)
VCC-RTC: C72.1, GPIO.7, R76.1, U1.M12 (VCC-RTC)
VCC-RTC_AXP: C102.2, R53.2, R56.2, R76.2, U6.46 (VCC_RTC)
VCC/2: 1.1V_CPU.1, C8.1, C9.1, C10.2, C11.2, C12.2, C94.2, L6.1, U1.E5 (VDD-CPU), U1.E6 (VDD-CPU), U1.E7 (VDD-CPU), U1.F5 (VDD-CPU), U1.F6 (VDD-CPU), U1.F7 (VDD-CPU), U1.G5 (VDD-CPU), U1.G6 (VDD-CPU), U6.38 (DCDC3)
VDD: 1.1V_SYS.1, C21.1, C22.1, C23.2, C24.2, C25.2, C83.2, C134.2, HSIC-1.1V.1, L5.1, U1.E8 (VDD-SYS), U1.E9 (VDD-SYS), U1.E10 (VDD-SYS), U1.K6 (VDD-SYS), U1.L6 (VDD-SYS), U1.M6 (VDD-SYS), U1.M7 (VDD-SYS), U1.N8 (VDD-SYS), U1.N9 (VDD-SYS), U1.N10 (VDD-SYS), U1.N12 (VCC-HSIC), U6.28 (DCDC2)
VEE: 2.8V_CSI.1, CSI/DSI.40, R63.1 (1.1)
VPP: 3.0VA.1, GPIO.5, R15.1, R32.2, R34.1, R64.1 (1.1)
VPS: R13.2, R16.1, U4.38 (NC)
XTALI: C66.2, Q1.2, U1.U4 (X24MIN)
XTALO: C67.2, Q1.1, U1.T4 (X24MOUT)

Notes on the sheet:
ANDROID SİSTEM REGULATORU
MicroSD-KART
NAND Flash -> Option!
32Gb (4096M x 8bit)
LED
TUSLAR
The power options are 4:
1. 5VEXT via PWR_JACK
2. BAT via LIPO_BAT
3. +5V_OTG_PWR via USB_OTG
(External 5VDC power source)
(External 4.2VDC battery)
(External 5VDC driven by any USB)
=======================
4. +5V via UART0 header
5V HARİCİ GÜÇ KAYNAĞI
8G Bytes NAND Flash
Debug UART
USB-OTG
LI-ION_BATTERY
4.2V
GENEL GIRIS-CIKIS PORT
DDR3 RAM BELLEK
Fiducials:
1GByte VE 2 GBYTE
CAMERA-CSI/MIPI-LCD-DSI
Audio Out & Mic
ALLWINNER A33 ANDROID TABLET 1-2 GB DDR3 RAM
MONITOR-LCD SOKET

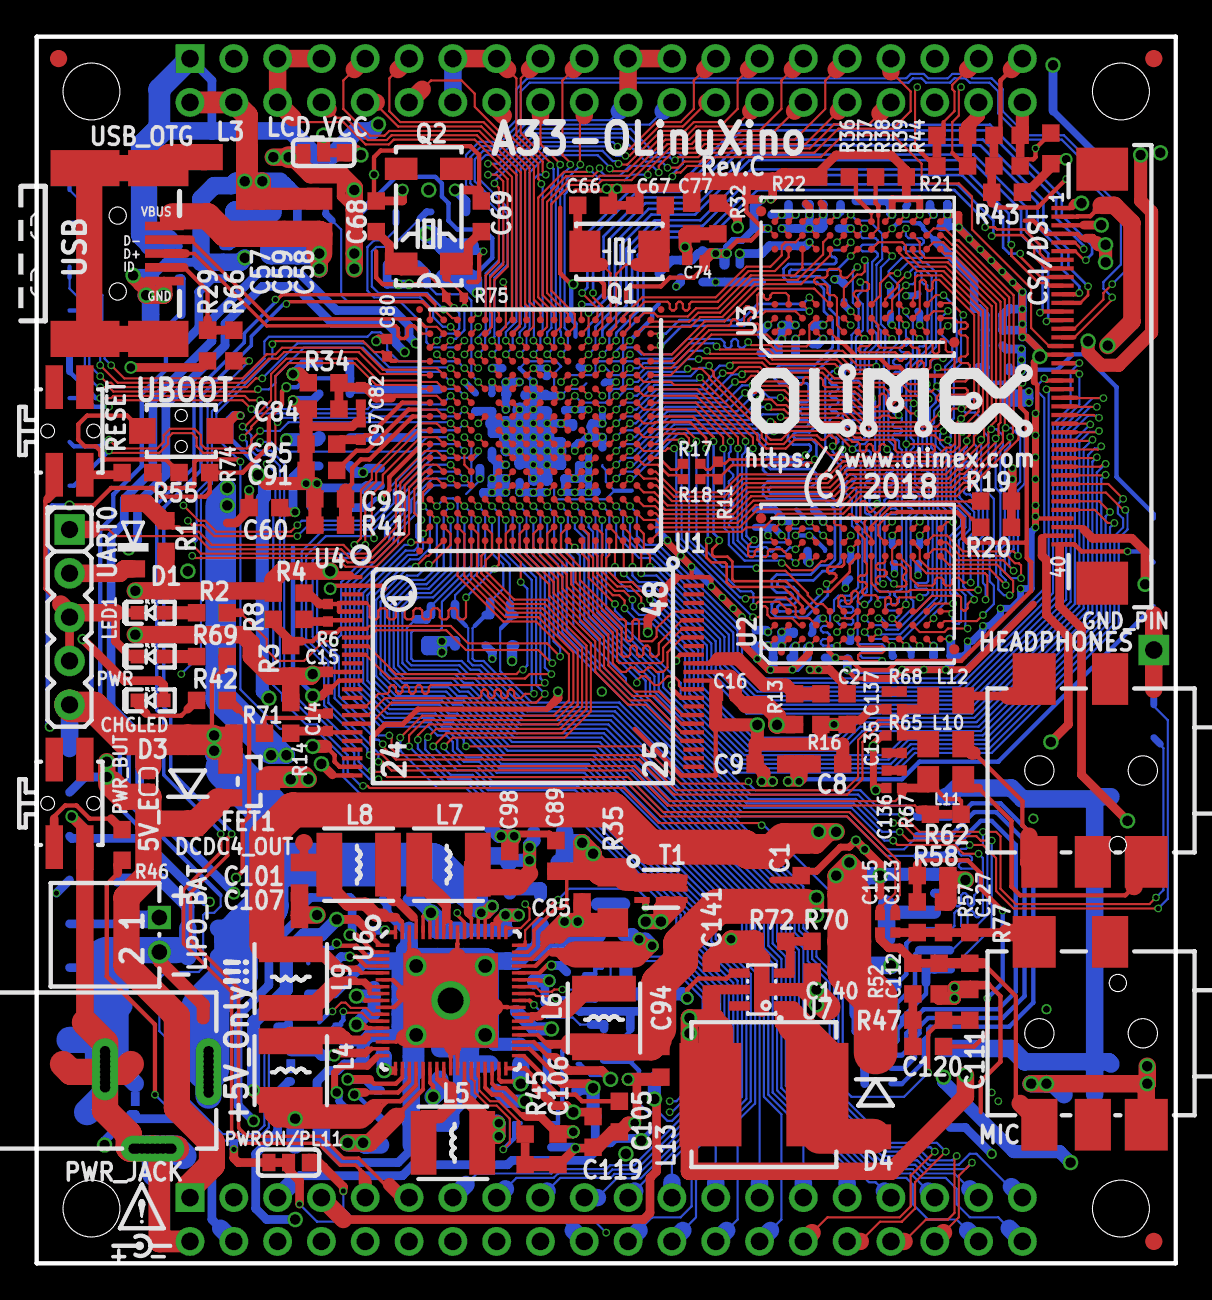
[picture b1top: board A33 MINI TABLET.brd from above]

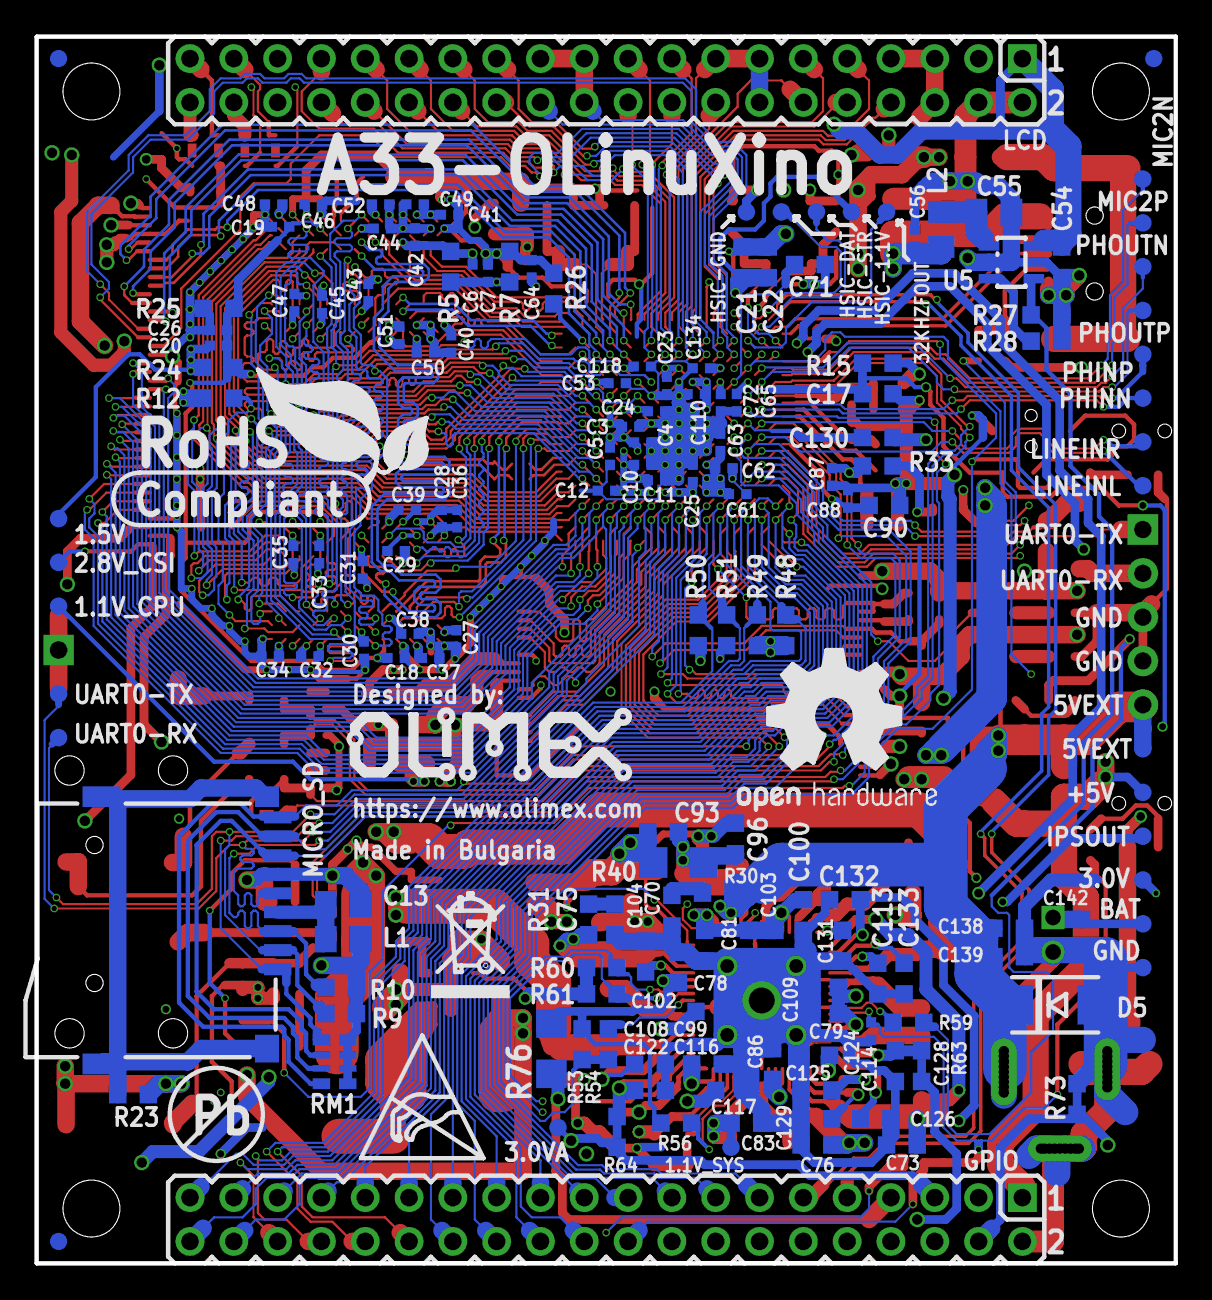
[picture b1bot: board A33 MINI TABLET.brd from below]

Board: 4 copper layers, 66.0 x 71.1 mm, 308 parts (170 on the bottom side), 301 nets.

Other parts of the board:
U$2: LOGO-OPENHARDWARE_8X8
U$3: ATTENTION_SMALL
U$6, U$8: OLIMEX1_V
U$9: PB
U$10: ESD_SYMBOL
U$11: RECYCLE_BIN1/8
U$12: ROHS

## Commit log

2024-09-16 LOKUM MINI TABLET (2GB LPDD3 HAFIZA) REV.A
    1.ALLWINNER A33 ARM CPU
    2.ANDROID 6.0 OS

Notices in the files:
ALLWINNER A33 MINI_TABLET/A33 MINI TABLET.brd:
(C) 2018
